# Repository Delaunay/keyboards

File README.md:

# Split v2 ZMK firmware

Wireless split firmware for the keyboard in `split/v2`. The dongle is the USB central. Each half is a nice!nano v2 peripheral, so neither half talks to the computer on its own.

The shield is written for the PCB as built: 6 columns, 5 rows, 4 thumb keys, and an EC11 encoder whose push switch sits on its own matrix row. Diodes point from column to row. The right half is this board mirrored, with its columns listed inner-to-outer so the keymap still reads left to right.

## Build

Pushing this repository runs `.github/workflows/build.yml`. The workflow builds four UF2 files:

| Artifact | Flash onto |
|---|---|
| `splitv2_dongle` | the dongle |
| `splitv2_left` | the left nice!nano |
| `splitv2_right` | the right nice!nano |
| `settings_reset` | each board, once, before the first real flash |

`build.yaml` uses `nice_nano//zmk` for the dongle, which is a nice!nano v2. If the dongle is a different BLE board, change that one `board:` line. The halves stay on `nice_nano//zmk`.

## First flash

1. Double-tap reset on a board so it shows up as a USB drive.
2. Copy `settings_reset` to that drive and wait for it to reboot. Do this for the dongle and both halves. It clears old Bluetooth bonds.
3. Flash `splitv2_dongle`, `splitv2_left`, and `splitv2_right` the same way.
4. Power the halves. They pair to the dongle by themselves.
5. Plug the dongle into the computer. It is the keyboard.

Later keymap edits only need the dongle reflashed. Pin or matrix changes need all three boards.

Hold the top-left key and tap the key under F1 to unlock [ZMK Studio](https://zmk.studio/) over USB. After Studio saves a keymap, further edits to `splitv2.keymap` are ignored until Studio's "Restore stock settings".

## Layout

Base layer, left then right:

```
Esc  F1 F2 F3 F4 F5          F6 F7 F8 F9 F10 F11
`    1  2  3  4  5           6  7  8  9  0   -
Tab  Q  W  E  R  T           Y  U  I  O  P   Bksp
Ctrl A  S  D  F  G           H  J  K  L  ;   '
Shft Z  X  C  V  B           N  M  ,  .  /   Shft
       Gui Bksp Space Nav    Sym Enter Space Alt
```

`Esc` is a layer-tap: tap for Escape, hold for the system layer. The left knob is volume, and its push is mute. The right knob is page up and page down, and its push is play/pause.

Hold `Nav` (left inner thumb) for arrows and a numpad. Hold `Sym` (right inner thumb) for symbols.

System layer, while holding the top-left key:

| Key | Action |
|---|---|
| F1 | unlock ZMK Studio |
| backtick | clear Bluetooth bonds on the dongle |
| 1 through 5 | Bluetooth profiles 0 through 4 |
| 6 | USB output |
| 7 | BLE output |
| right Shift | dongle bootloader |

To put a half into the bootloader, double-tap its reset button. The bootloader key only resets the dongle, because that is where the keymap runs.

## Power

The AAA holder on the PCB is tied to the nice!nano RAW / VDDH pad. That pad is the LiPo input. A single AAA cell is below the voltage the nice!nano expects there, and the onboard charger is for a lithium battery. Power each half with a LiPo on the battery pads.

## If a side feels backwards

The right knob's A and B pins are swapped in `splitv2_right.overlay` so clockwise matches the left knob. If the right knob goes the wrong way, swap those two `gpios` lines back.

A 30-detent encoder is set to `steps = <120>` and 30 triggers per turn. If one click does nothing, or fires twice, try `steps` of 60 or 80 in `splitv2.dtsi`.

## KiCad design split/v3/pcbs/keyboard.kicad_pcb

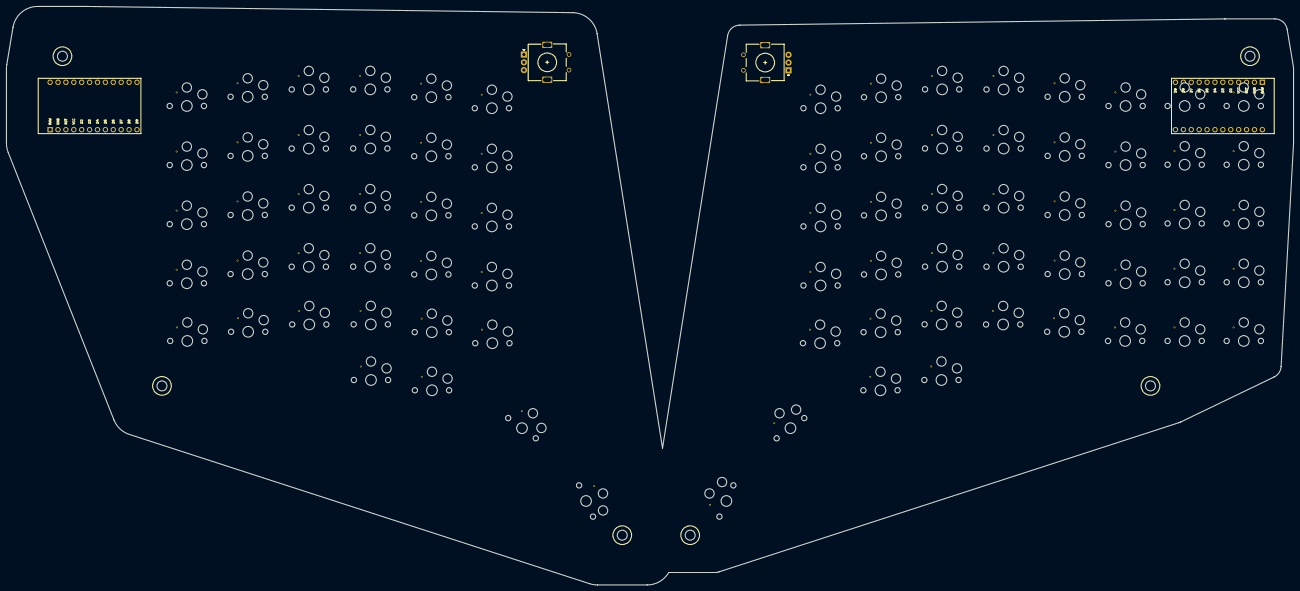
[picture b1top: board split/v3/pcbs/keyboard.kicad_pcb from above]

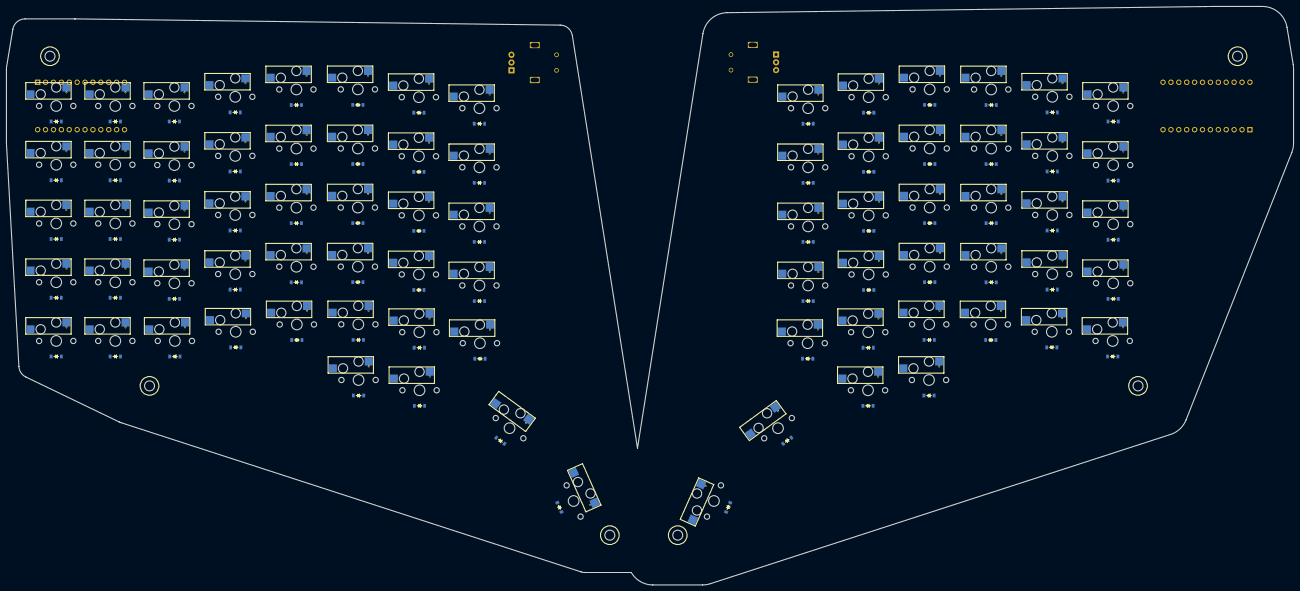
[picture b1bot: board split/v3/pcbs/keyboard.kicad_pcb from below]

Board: 2 copper layers, 413.8 x 186.0 mm, 244 parts (156 on the bottom side), 112 nets, no tracks yet.

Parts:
D1, D2, D3, D4, D5, D6, D7, D8, D9, D10, D11, D12, D13, D14, D15, D16, D17, D18, D19, D20, D21, D22, D23, D24, D25, D26, D27, D28, D29, D30, D31, D32, D33, D34, D35, D36, D37, D38, D39, D40, D41, D42, D43, D44, D45, D46, D47, D48, D49, D50, D51, D52, D53, D54, D55, D56, D57, D58, D59, D60, D61, D62, D63, D64, D65, D66, D67, D68, D69, D70, D71, D72, D73, D74, D75, D76, D77, D78: Diode_SMD_B
H1, H2, H3, H4, H5, H6: M3
HS1, HS2, HS3, HS4, HS5, HS6, HS7, HS8, HS9, HS10, HS11, HS12, HS13, HS14, HS15, HS16, HS17, HS18, HS19, HS20, HS21, HS22, HS23, HS24, HS25, HS26, HS27, HS28, HS29, HS30, HS31, HS32, HS33, HS34, HS35, HS36, HS37, HS38, HS39, HS40, HS41, HS42, HS43, HS44, HS45, HS46, HS47, HS48, HS49, HS50, HS51, HS52, HS53, HS54, HS55, HS56, HS57, HS58, HS59, HS60, HS61, HS62, HS63, HS64, HS65, HS66, HS67, HS68, HS69, HS70, HS71, HS72, HS73, HS74, HS75, HS76, HS77, HS78: Kailh_Choc_Hotswap
MCU1, MCU2: nice_nano_v2
ROT1, ROT2: rotary_encoder
S1, S2, S3, S4, S5, S6, S7, S8, S9, S10, S11, S12, S13, S14, S15, S16, S17, S18, S19, S20, S21, S22, S23, S24, S25, S26, S27, S28, S29, S30, S31, S32, S33, S34, S35, S36, S37, S38, S39, S40, S41, S42, S43, S44, S45, S46, S47, S48, S49, S50, S51, S52, S53, S54, S55, S56, S57, S58, S59, S60, S61, S62, S63, S64, S65, S66, S67, S68, S69, S70, S71, S72, S73, S74, S75, S76, S77, S78: Kailh_PG1350; PG1350

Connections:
L_COL_INDEX: HS5.1, HS11.1, HS17.1, HS23.1, HS29.1, HS33.1, MCU1.19
L_COL_INNER: HS6.1, HS12.1, HS18.1, HS24.1, HS30.1, MCU1.17
L_COL_MACRO: HS1.1, HS7.1, HS13.1, HS19.1, HS25.1, MCU1.22
L_COL_MIDDLE: HS4.1, HS10.1, HS16.1, HS22.1, HS28.1, HS32.1, MCU1.20
L_COL_PINKY: HS2.1, HS8.1, HS14.1, HS20.1, HS26.1, MCU1.11
L_COL_RING: HS3.1, HS9.1, HS15.1, HS21.1, HS27.1, HS31.1, MCU1.21
L_GND: MCU1.2, MCU1.15, MCU1.16, ROT1.2, ROT1.C
L_P8: MCU1.23, ROT1.B
L_P9: MCU1.24, ROT1.1
L_P20: MCU1.6, ROT1.A
L_ROW_BOT: D1.1, D2.1, D3.1, D4.1, D5.1, D6.1, MCU1.12
L_ROW_FN: D25.1, D26.1, D27.1, D28.1, D29.1, D30.1, MCU1.7
L_ROW_HOME: D7.1, D8.1, D9.1, D10.1, D11.1, D12.1, MCU1.10
L_ROW_NUMS: D19.1, D20.1, D21.1, D22.1, D23.1, D24.1, MCU1.8
L_ROW_THUMB: D31.1, D32.1, D33.1, D34.1, MCU1.18
L_ROW_TOP: D13.1, D14.1, D15.1, D16.1, D17.1, D18.1, MCU1.9
R_COL_BRACKET: HS35.1, HS36.1, HS37.1, HS38.1, HS39.1, MCU2.13
R_COL_INDEX: HS49.1, HS55.1, HS61.1, HS67.1, HS73.1, HS77.1, MCU2.19
R_COL_INNER: HS50.1, HS56.1, HS62.1, HS68.1, HS74.1, MCU2.17
R_COL_MACRO: HS45.1, HS51.1, HS57.1, HS63.1, HS69.1, MCU2.22
R_COL_MIDDLE: HS48.1, HS54.1, HS60.1, HS66.1, HS72.1, HS76.1, MCU2.20
R_COL_NAV: HS40.1, HS41.1, HS42.1, HS43.1, HS44.1, MCU2.5
R_COL_PINKY: HS46.1, HS52.1, HS58.1, HS64.1, HS70.1, MCU2.11
R_COL_RING: HS47.1, HS53.1, HS59.1, HS65.1, HS71.1, HS75.1, MCU2.21
R_GND: MCU2.2, MCU2.15, MCU2.16, ROT2.2, ROT2.C
R_P8: MCU2.23, ROT2.B
R_P9: MCU2.24, ROT2.1
R_P20: MCU2.6, ROT2.A
R_ROW_BOT: D35.1, D40.1, D45.1, D46.1, D47.1, D48.1, D49.1, D50.1, MCU2.12
R_ROW_FN: D39.1, D44.1, D69.1, D70.1, D71.1, D72.1, D73.1, D74.1, MCU2.7
R_ROW_HOME: D36.1, D41.1, D51.1, D52.1, D53.1, D54.1, D55.1, D56.1, MCU2.10
R_ROW_NUMS: D38.1, D43.1, D63.1, D64.1, D65.1, D66.1, D67.1, D68.1, MCU2.8
R_ROW_THUMB: D75.1, D76.1, D77.1, D78.1, MCU2.18
R_ROW_TOP: D37.1, D42.1, D57.1, D58.1, D59.1, D60.1, D61.1, D62.1, MCU2.9
matrix_bracket_bottom_at: D35.2, HS35.2
matrix_bracket_fn_at: D39.2, HS39.2
matrix_bracket_home_at: D36.2, HS36.2
matrix_bracket_nums_at: D38.2, HS38.2
matrix_bracket_top_at: D37.2, HS37.2
matrix_index_bottom_at: D5.2, HS5.2
matrix_index_fn_at: D29.2, HS29.2
matrix_index_home_at: D11.2, HS11.2
matrix_index_nums_at: D23.2, HS23.2
matrix_index_top_at: D17.2, HS17.2
matrix_inner_bottom_at: D6.2, HS6.2
matrix_inner_fn_at: D30.2, HS30.2
matrix_inner_home_at: D12.2, HS12.2
matrix_inner_nums_at: D24.2, HS24.2
matrix_inner_top_at: D18.2, HS18.2
matrix_macro_bottom_at: D1.2, HS1.2
matrix_macro_fn_at: D25.2, HS25.2
matrix_macro_home_at: D7.2, HS7.2
matrix_macro_nums_at: D19.2, HS19.2
matrix_macro_top_at: D13.2, HS13.2
matrix_middle_bottom_at: D4.2, HS4.2
matrix_middle_fn_at: D28.2, HS28.2
matrix_middle_home_at: D10.2, HS10.2
matrix_middle_nums_at: D22.2, HS22.2
matrix_middle_top_at: D16.2, HS16.2
matrix_nav_bottom_at: D40.2, HS40.2
matrix_nav_fn_at: D44.2, HS44.2
matrix_nav_home_at: D41.2, HS41.2
matrix_nav_nums_at: D43.2, HS43.2
matrix_nav_top_at: D42.2, HS42.2
matrix_pinky_bottom_at: D2.2, HS2.2
matrix_pinky_fn_at: D26.2, HS26.2
matrix_pinky_home_at: D8.2, HS8.2
matrix_pinky_nums_at: D20.2, HS20.2
matrix_pinky_top_at: D14.2, HS14.2
matrix_ring_bottom_at: D3.2, HS3.2
matrix_ring_fn_at: D27.2, HS27.2
matrix_ring_home_at: D9.2, HS9.2
matrix_ring_nums_at: D21.2, HS21.2
matrix_ring_top_at: D15.2, HS15.2
mirror_matrix_index_bottom_at: D49.2, HS49.2
mirror_matrix_index_fn_at: D73.2, HS73.2
mirror_matrix_index_home_at: D55.2, HS55.2
mirror_matrix_index_nums_at: D67.2, HS67.2
mirror_matrix_index_top_at: D61.2, HS61.2
mirror_matrix_inner_bottom_at: D50.2, HS50.2
mirror_matrix_inner_fn_at: D74.2, HS74.2
mirror_matrix_inner_home_at: D56.2, HS56.2
mirror_matrix_inner_nums_at: D68.2, HS68.2
mirror_matrix_inner_top_at: D62.2, HS62.2
mirror_matrix_macro_bottom_at: D45.2, HS45.2
mirror_matrix_macro_fn_at: D69.2, HS69.2
mirror_matrix_macro_home_at: D51.2, HS51.2
mirror_matrix_macro_nums_at: D63.2, HS63.2
mirror_matrix_macro_top_at: D57.2, HS57.2
mirror_matrix_middle_bottom_at: D48.2, HS48.2
mirror_matrix_middle_fn_at: D72.2, HS72.2
mirror_matrix_middle_home_at: D54.2, HS54.2
mirror_matrix_middle_nums_at: D66.2, HS66.2
mirror_matrix_middle_top_at: D60.2, HS60.2
mirror_matrix_pinky_bottom_at: D46.2, HS46.2
mirror_matrix_pinky_fn_at: D70.2, HS70.2
mirror_matrix_pinky_home_at: D52.2, HS52.2
mirror_matrix_pinky_nums_at: D64.2, HS64.2
mirror_matrix_pinky_top_at: D58.2, HS58.2
mirror_matrix_ring_bottom_at: D47.2, HS47.2
mirror_matrix_ring_fn_at: D71.2, HS71.2
mirror_matrix_ring_home_at: D53.2, HS53.2
mirror_matrix_ring_nums_at: D65.2, HS65.2
mirror_matrix_ring_top_at: D59.2, HS59.2
mirror_thumbs_index_thumb_at: D77.2, HS77.2
mirror_thumbs_middle_thumb_at: D76.2, HS76.2
mirror_thumbs_ring_thumb_at: D75.2, HS75.2
mirror_thumbs_thumb5_thumb_at: D78.2, HS78.2
thumbs_index_thumb_at: D33.2, HS33.2
thumbs_middle_thumb_at: D32.2, HS32.2
thumbs_ring_thumb_at: D31.2, HS31.2
thumbs_thumb5_thumb_at: D34.2, HS34.2

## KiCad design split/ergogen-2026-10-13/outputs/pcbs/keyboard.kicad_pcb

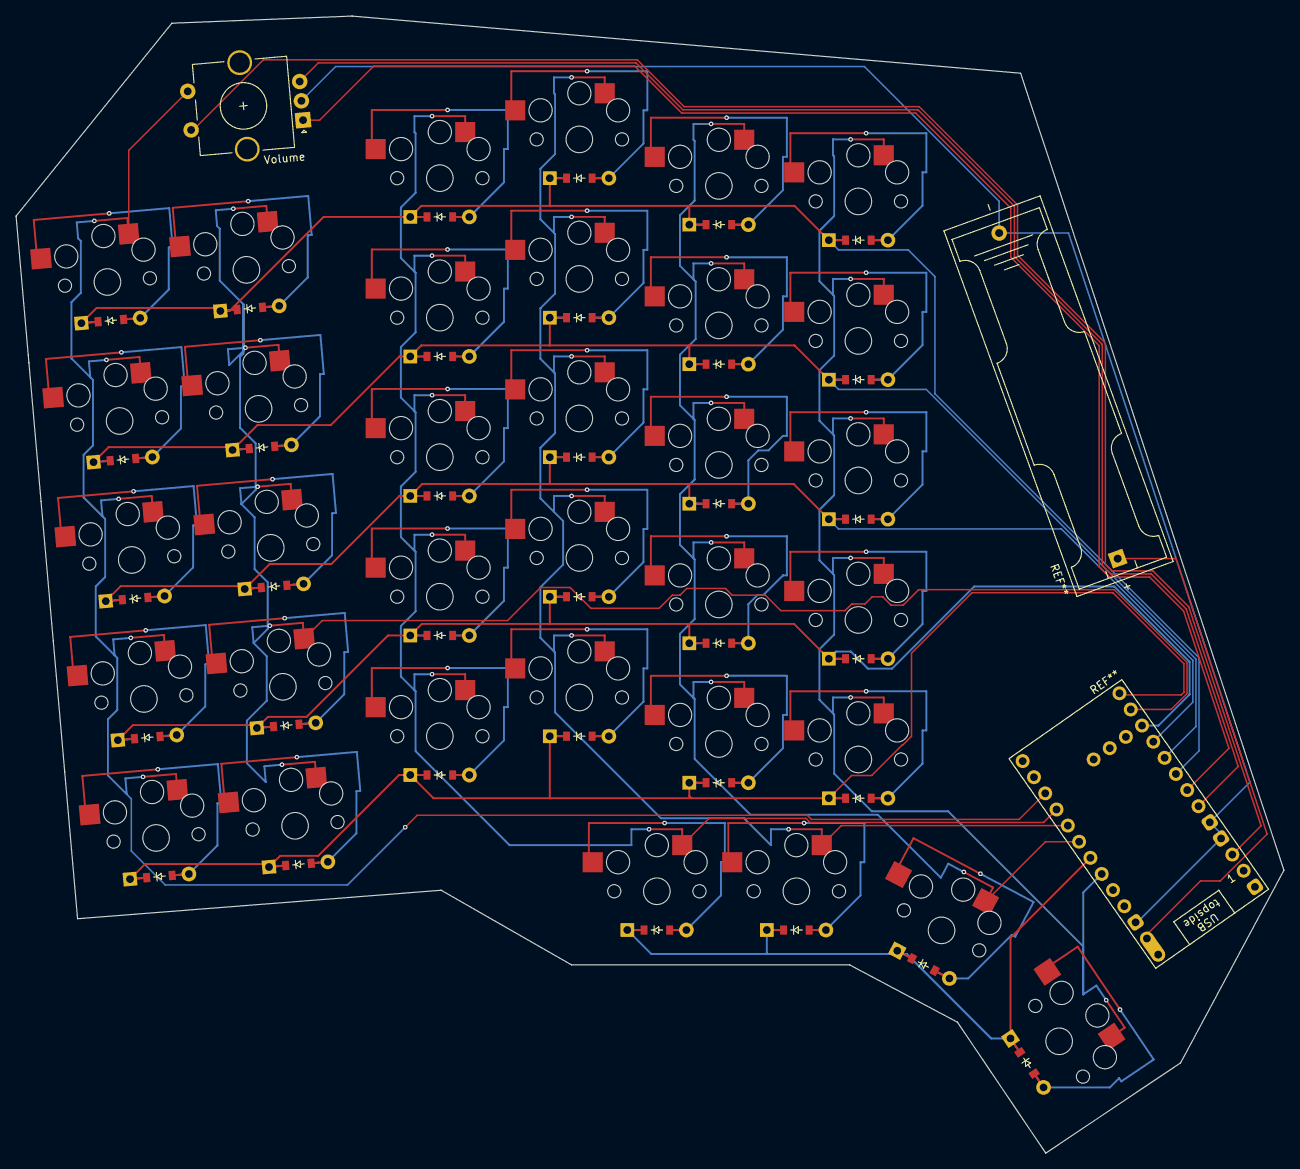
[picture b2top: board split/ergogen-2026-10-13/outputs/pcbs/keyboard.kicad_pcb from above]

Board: 2 copper layers, 163.6 x 146.7 mm, 69 parts (0 on the bottom side), 46 nets.

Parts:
D1, D2, D3, D4, D5, D6, D7, D8, D9, D10, D11, D12, D13, D14, D15, D16, D17, D18, D19, D20, D21, D22, D23, D24, D25, D26, D27, D28, D29, D30, D31, D32, D33, D34: ComboDiode
S1, S2, S3, S4, S5, S6, S7, S8, S9, S10, S11, S12, S13, S14, S15, S16, S17, S18, S19, S20, S21, S22, S23, S24, S25, S26, S27, S28, S29, S30, S31, S32, S33, S34: PG1350
Volume: Encoder; RotaryEncoder_Alps_EC11E-Switch_Vertical_H20mm_CircularMoun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

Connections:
COL_INDEX: S21.1, S22.1, S23.1, S24.1, S25.1, S33.1
COL_INNER: S26.1, S27.1, S28.1, S29.1, S30.1, S34.1
COL_MACRO: S1.1, S2.1, S3.1, S4.1, S5.1, Volume.S1
COL_MIDDLE: S16.1, S17.1, S18.1, S19.1, S20.1, S32.1
COL_PINKY: S6.1, S7.1, S8.1, S9.1, S10.1
COL_RING: S11.1, S12.1, S13.1, S14.1, S15.1, S31.1
ROW_BOT: D1.1, D6.1, D11.1, D16.1, D21.1, D26.1
ROW_FN: D5.1, D10.1, D15.1, D20.1, D25.1, D30.1
ROW_HOME: D2.1, D7.1, D12.1, D17.1, D22.1, D27.1
ROW_NUMS: D4.1, D9.1, D14.1, D19.1, D24.1, D29.1
ROW_THUMB: D31.1, D32.1, D33.1, D34.1
ROW_TOP: D3.1, D8.1, D13.1, D18.1, D23.1, D28.1
far_thumb: D34.2, S34.2
home_thumb: D33.2, S33.2
index_bottom: D21.2, S21.2
index_fn: D25.2, S25.2
index_home: D22.2, S22.2
index_nums: D24.2, S24.2
index_top: D23.2, S23.2
inner_bottom: D26.2, S26.2
inner_fn: D30.2, S30.2
inner_home: D27.2, S27.2
inner_nums: D29.2, S29.2
inner_top: D28.2, S28.2
macro_bottom: D1.2, S1.2
macro_fn: D5.2, S5.2
macro_home: D2.2, S2.2
macro_nums: D4.2, S4.2
macro_top: D3.2, S3.2
middle_bottom: D16.2, S16.2
middle_fn: D20.2, S20.2
middle_home: D17.2, S17.2
middle_nums: D19.2, S19.2
middle_top: D18.2, S18.2
near_thumb: D32.2, S32.2
nearest_thumb: D31.2, S31.2
pinky_bottom: D6.2, S6.2
pinky_fn: D10.2, S10.2
pinky_home: D7.2, S7.2
pinky_nums: D9.2, S9.2
pinky_top: D8.2, S8.2
ring_bottom: D11.2, S11.2
ring_fn: D15.2, S15.2
ring_home: D12.2, S12.2
ring_nums: D14.2, S14.2
ring_top: D13.2, S13.2

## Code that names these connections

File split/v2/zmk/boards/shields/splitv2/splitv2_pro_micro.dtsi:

/*
 * Copyright (c) 2026 The ZMK Contributors
 * SPDX-License-Identifier: MIT
 *
 * Matrix and encoders for the nice!nano v2 halves.
 * The XIAO BLE dongle does not include this file. It has no pro_micro node.
 *
 * nice!nano v2 Pro Micro pads, USB at the top.
 * Left row, top to bottom, is pads 1-12. Right row is pads 13-24.
 *   pad 2   D0   ENC_BTN   encoder push, extra matrix row on COL_MACRO
 *   pad 5   D2   ENC_B
 *   pad 6   D3   ENC_A
 *   pad 7   D4   ROW_FN
 *   pad 8   D5   ROW_NUMS
 *   pad 9   D6   ROW_TOP
 *   pad 10  D7   ROW_HOME
 *   pad 11  D8   COL_PINKY
 *   pad 12  D9   ROW_BOT
 *   pad 17  A3   COL_INNER
 *   pad 18  A2   ROW_THUMB
 *   pad 19  A1   COL_INDEX
 *   pad 20  A0   COL_MIDDLE
 *   pad 21  D15  COL_RING
 *   pad 22  D14  COL_MACRO
 *
 * The encoder push is wired between COL_MACRO and D0, with no diode.
 * D0 is scanned as its own row, so only the macro column has that key.
 *
 * steps = 120 and 30 triggers match a 30-detent EC11 (4 counts per detent).
 * If a click does nothing or fires twice, try steps of 60 or 80.
 */

/ {
    chosen {
        zmk,kscan = &kscan0;
    };

    kscan0: kscan0 {
        compatible = "zmk,kscan-gpio-matrix";
        diode-direction = "col2row";
        wakeup-source;

        row-gpios
            = <&pro_micro 4 (GPIO_ACTIVE_HIGH | GPIO_PULL_DOWN)>  /* ROW_FN    */
            , <&pro_micro 5 (GPIO_ACTIVE_HIGH | GPIO_PULL_DOWN)>  /* ROW_NUMS  */
            , <&pro_micro 6 (GPIO_ACTIVE_HIGH | GPIO_PULL_DOWN)>  /* ROW_TOP   */
            , <&pro_micro 7 (GPIO_ACTIVE_HIGH | GPIO_PULL_DOWN)>  /* ROW_HOME  */
            , <&pro_micro 9 (GPIO_ACTIVE_HIGH | GPIO_PULL_DOWN)>  /* ROW_BOT   */
            , <&pro_micro 20 (GPIO_ACTIVE_HIGH | GPIO_PULL_DOWN)> /* ROW_THUMB */
            , <&pro_micro 0 (GPIO_ACTIVE_HIGH | GPIO_PULL_DOWN)>  /* ENC_BTN   */
            ;

        col-gpios
            = <&pro_micro 14 GPIO_ACTIVE_HIGH> /* COL_MACRO  */
            , <&pro_micro 8 GPIO_ACTIVE_HIGH>  /* COL_PINKY  */
            , <&pro_micro 15 GPIO_ACTIVE_HIGH> /* COL_RING   */
            , <&pro_micro 18 GPIO_ACTIVE_HIGH> /* COL_MIDDLE */
            , <&pro_micro 19 GPIO_ACTIVE_HIGH> /* COL_INDEX  */
            , <&pro_micro 21 GPIO_ACTIVE_HIGH> /* COL_INNER  */
            ;
    };

    left_encoder: encoder_left {
        compatible = "alps,ec11";
        a-gpios = <&pro_micro 3 (GPIO_ACTIVE_HIGH | GPIO_PULL_UP)>;
        b-gpios = <&pro_micro 2 (GPIO_ACTIVE_HIGH | GPIO_PULL_UP)>;
        steps = <120>;
        status = "disabled";
    };

    right_encoder: encoder_right {
        compatible = "alps,ec11";
        a-gpios = <&pro_micro 3 (GPIO_ACTIVE_HIGH | GPIO_PULL_UP)>;
        b-gpios = <&pro_micro 2 (GPIO_ACTIVE_HIGH | GPIO_PULL_UP)>;
        steps = <120>;
        status = "disabled";
    };
};
